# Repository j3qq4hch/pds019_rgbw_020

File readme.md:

# PDS019_lit20

В этом репозитории содержатся исходники устройства PDS019_rgbw_020.

Конструктивно устройство представляет из себя две печатные платы, размещенные в корпусе для монтажа на DIN-рейку [GAINTA D4MG](https://www.gainta.com/en/d4mg.html)

# Внешний вид платы А (верхней платы)

# Внешний вид платы B (нижней платы)

> [!IMPORTANT]
> Исходная документация (включая производственную документацию) хранится [здесь](https://github.com/j3qq4hch/pds019_rgbw_020/issues/1).

3d модель для онлайн просмотра доступна [по ссылке](https://a360.co/4bYYxEc)

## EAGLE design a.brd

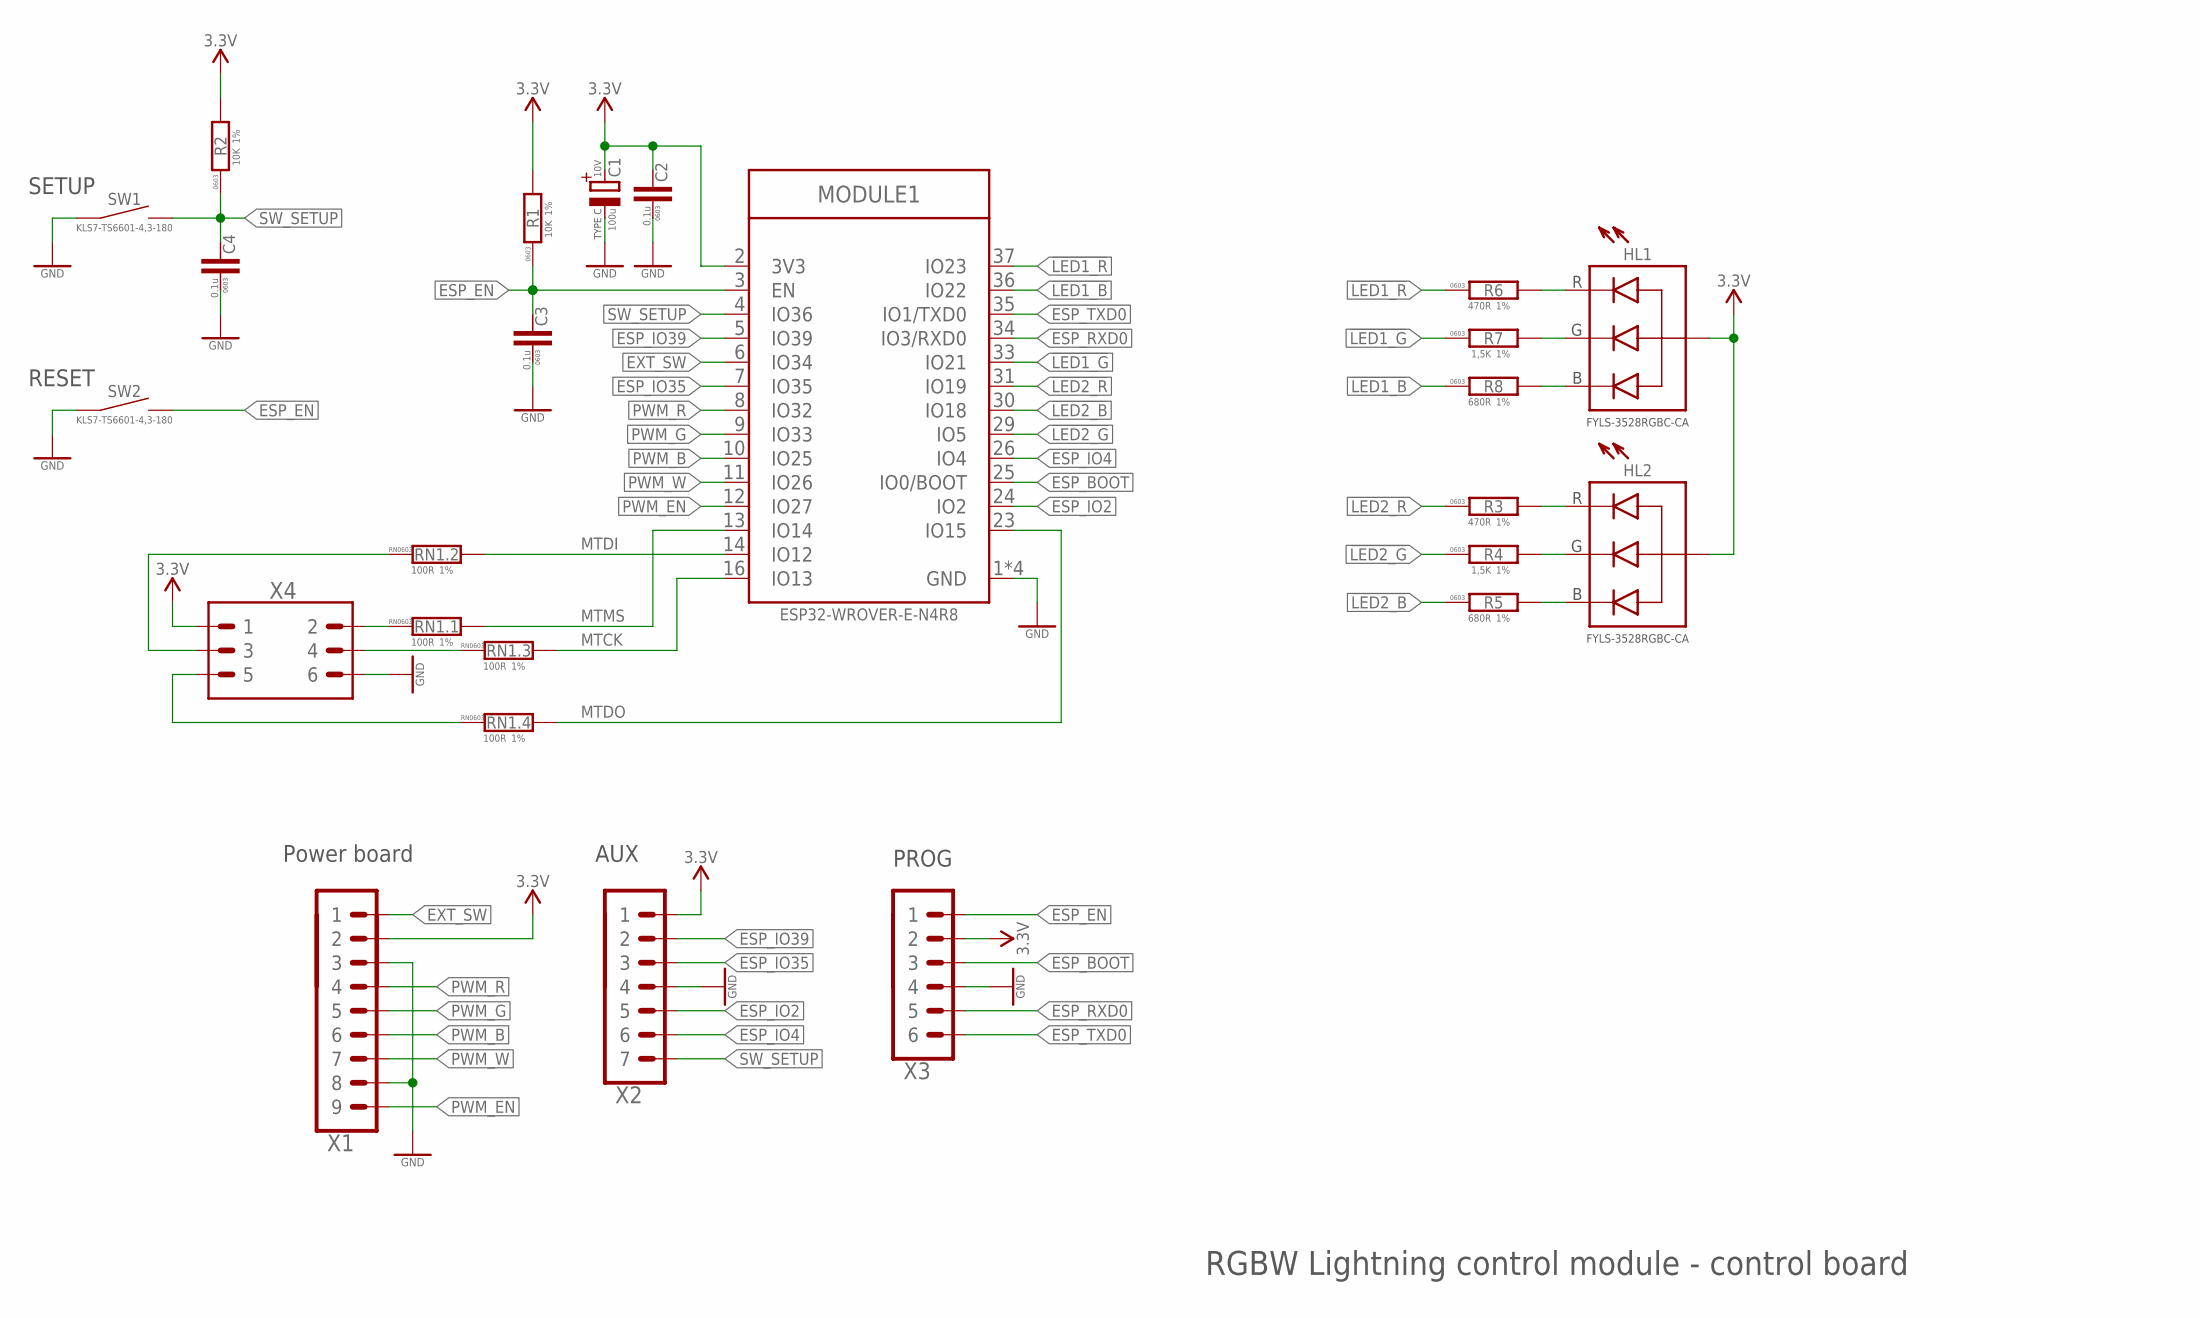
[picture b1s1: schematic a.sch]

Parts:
C1: 100u; CTANT_TYPE_C; VOLTAGE 10V
C2, C3, C4: 0.1u; C0603
HL1, HL2: LED_RGB-3528; LED3528
MODULE1: ESP32-WROVER-(I)E; ESP32-WROVER-E
R1, R2: 10K; R0603
R3, R6: 470R; R0603
R4, R7: 1,5K; R0603
R5, R8: 680R; R0603
RN1: 100R; R_4X0603
SW1, SW2: TS6601-9,5; SW4-6.0X6.0X5.0MM
X1: PINHEAD_1X09-2.54-TH-MALE; 1X09-PTH-2.54
X2: PINHEAD_1X07-2.54; 1X07-PTH-2.54
X3: PINHEAD_1X06-2-MALE; 1X06-PTH-2
X4: PINHEAD_2X03-PTH-2.54; 2X03-PTH-2.54

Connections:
!LED1_B: MODULE1.36 (IO22), R8.1
!LED1_G: MODULE1.33 (IO21), R7.1
!LED1_R: MODULE1.37 (IO23), R6.1
!LED2_B: MODULE1.30 (IO18), R5.1
!LED2_G: MODULE1.29 (IO5), R4.1
!LED2_R: MODULE1.31 (IO19), R3.1
ESP_BOOT: MODULE1.25 (IO0/BOOT), X3.3
ESP_EN: C3.2, MODULE1.3 (EN), R1.1, SW2.2, SW2.3 (2), X3.1
ESP_IO2: MODULE1.24 (IO2), X2.5
ESP_IO4: MODULE1.26 (IO4), X2.6
ESP_IO35: MODULE1.7 (IO35), X2.3
ESP_IO39: MODULE1.5 (IO39), X2.2
ESP_RXD0: MODULE1.34 (IO3/RXD0), X3.5
ESP_TXD0: MODULE1.35 (IO1/TXD0), X3.6
EXT_SW: MODULE1.6 (IO34), X1.1
GND: C1.-, C2.1, C3.1, C4.1, MODULE1.1 (GND), MODULE1.15 (GND), MODULE1.38 (GND), MODULE1.39 (GND), SW1.1, SW1.4 (1), SW2.1, SW2.4 (1), X1.3, X1.8, X2.4, X3.4, X4.6
MTCK: MODULE1.16 (IO13), RN1.6 (2)
MTDI: MODULE1.14 (IO12), RN1.7 (2)
MTDI_J: RN1.2 (1), X4.3
MTDO: MODULE1.23 (IO15), RN1.5 (2)
MTMS: MODULE1.13 (IO14), RN1.8 (2)
unnamed: HL2.1 (R), R3.2
unnamed: HL1.4 (G), R7.2
unnamed: HL1.1 (R), R6.2
unnamed: HL1.3 (B), R8.2
unnamed: HL2.4 (G), R4.2
unnamed: RN1.1, X4.2
unnamed: RN1.3 (1), X4.4
unnamed: RN1.4 (1), X4.5
unnamed: HL2.3 (B), R5.2
PWM_B: MODULE1.10 (IO25), X1.6
PWM_EN: MODULE1.12 (IO27), X1.9
PWM_G: MODULE1.9 (IO33), X1.5
PWM_R: MODULE1.8 (IO32), X1.4
PWM_W: MODULE1.11 (IO26), X1.7
SW_SETUP: C4.2, MODULE1.4 (IO36), R2.1, SW1.2, SW1.3 (2), X2.7
VDD_3V3: C1.+, C2.2, HL1.2 (A), HL2.2 (A), MODULE1.2 (3V3), R1.2, R2.2, X1.2, X2.1, X3.2, X4.1

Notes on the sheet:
RESET
SETUP
PROG
Power board
RGBW Lightning control module - control board
AUX

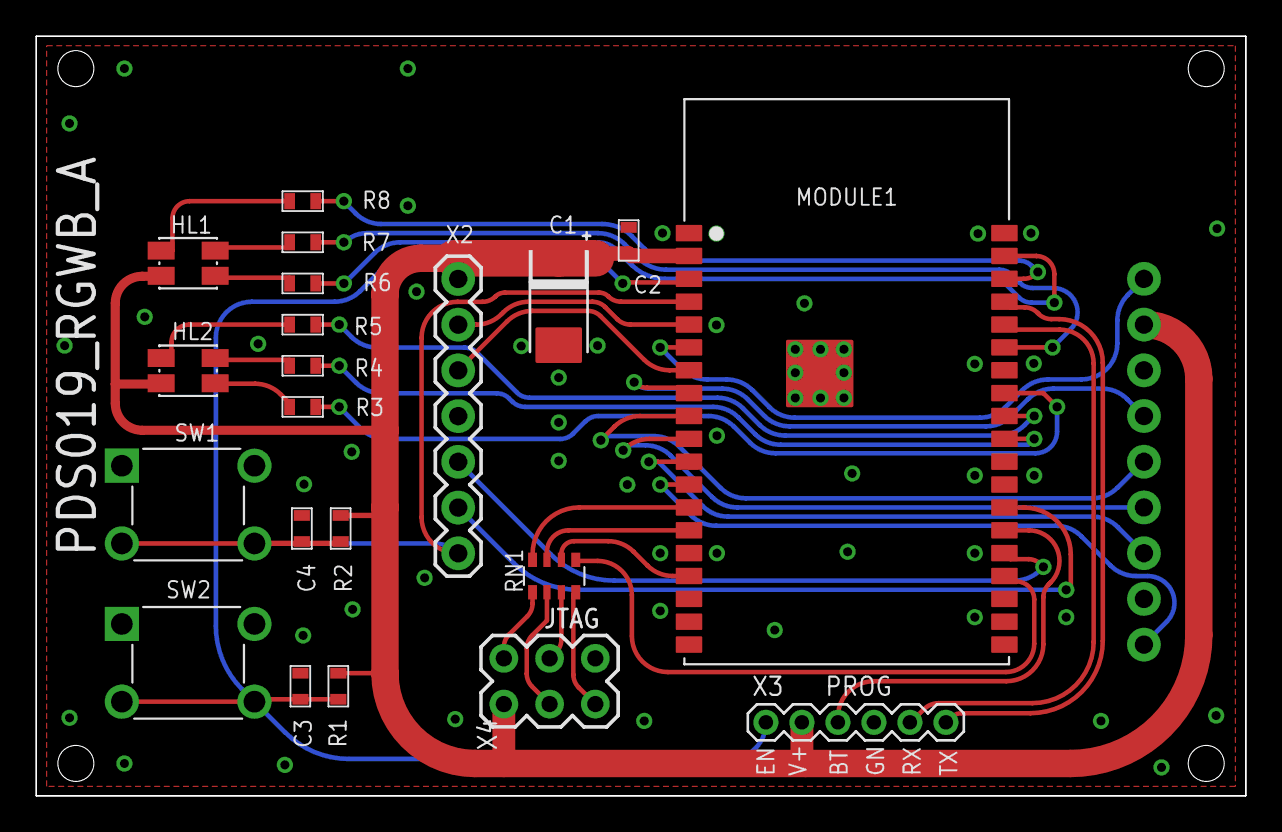
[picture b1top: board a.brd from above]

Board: 2 copper layers, 67.2 x 42.2 mm, 23 parts (1 on the bottom side), 37 nets.

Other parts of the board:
PCB1: D4MG_PCB_UP

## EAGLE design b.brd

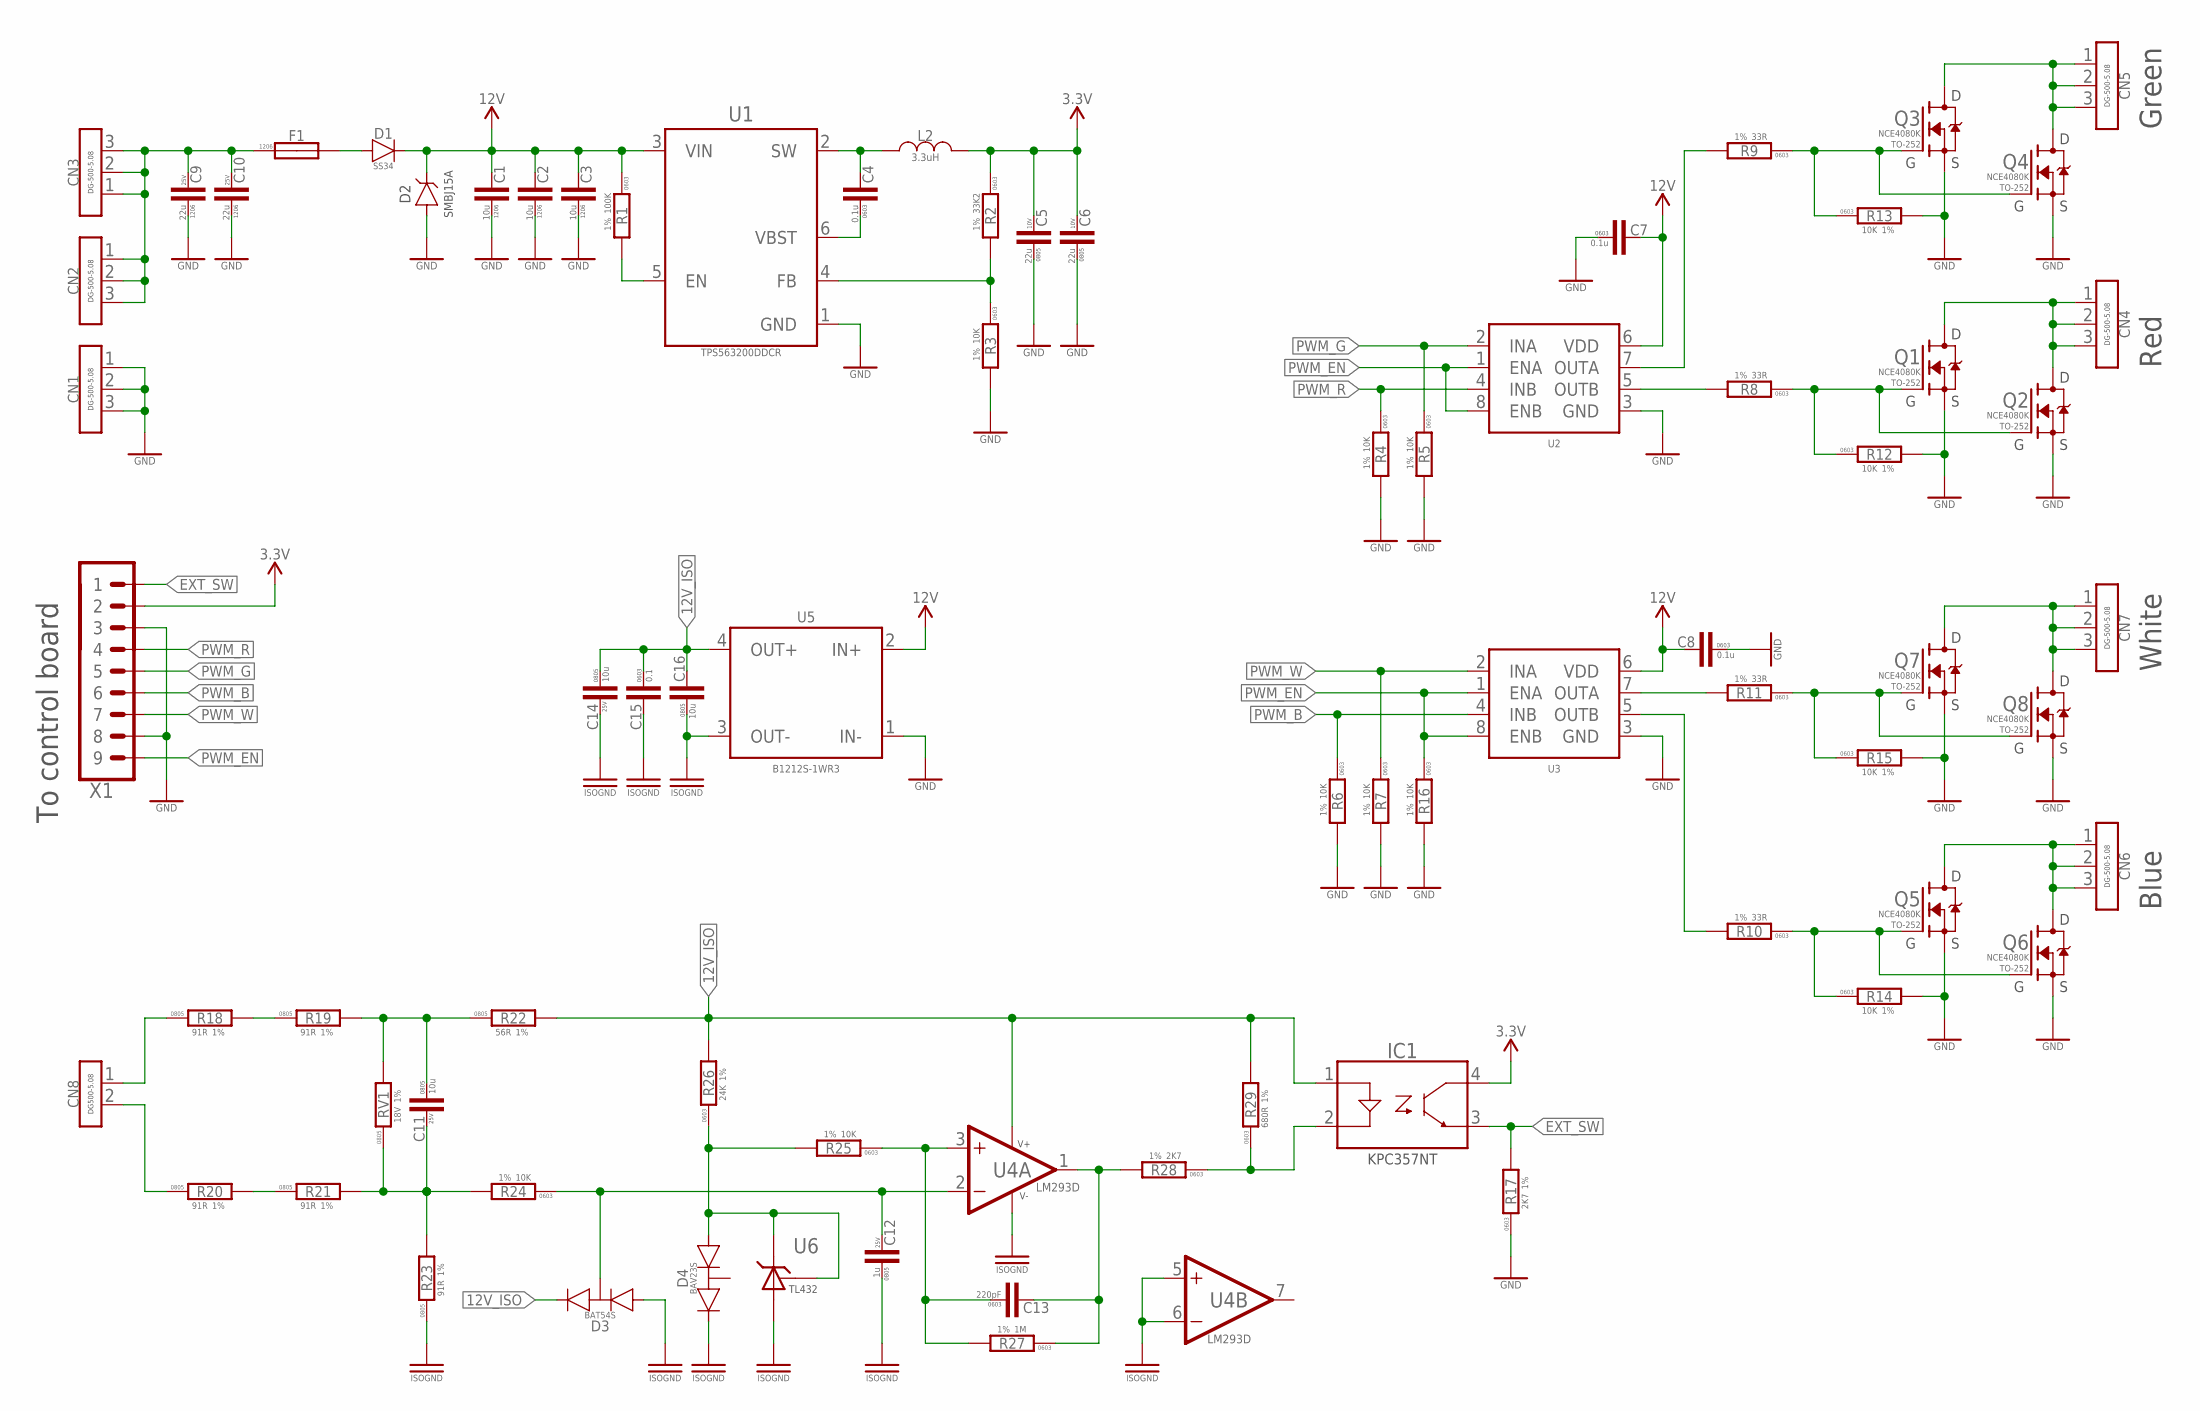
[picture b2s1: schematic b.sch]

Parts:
C1, C2, C3: 10u; C1206
C4, C7, C8: 0.1u; C0603
C5, C6: 22u; C0805; VOLTAGE 10V
C9, C10: 22u; C1206; VOLTAGE 25V
C11, C14: 10u; C0805; VOLTAGE 25V
C12: 1u; C0805; VOLTAGE 25V
C13: 220pF; C0603
C15: 0.1; C0603
C16: 10u; C0805
CN1, CN2, CN3, CN4, CN5, CN6, CN7: CON-3P-DG500-5.08; DG500-5.08-03P
CN8: DG508V-2P; DG500-5.08-02P
D1: SS24; DO-214AC(SMA)
D2: SMBJ15A-SMB; DO-214AA(SMB)
D3: BAT54S; SOT23
D4: BAV23S-SOT23; SOT23
F1: eFUSE-1206-500mA; F1206
IC1: KPC357NT-SOP-4; -SOP-4
L2: 3.3uH; SWPA6020
Q1, Q2, Q3, Q4, Q5, Q6, Q7, Q8: 100N04; D-PAK
R1: 100K; R0603
R2: 33K2; R0603
R3, R4, R5, R6, R7, R12, R13, R14, R15, R16, R24, R25: 10K; R0603
R8, R9, R10, R11: 33R; R0603
R17, R28: 2K7; R0603
R18, R19, R20, R21, R23: 91R; R0805
R22: 56R; R0805
R26: 24K; R0603
R27: 1M; R0603
R29: 680R; R0603
RV1: 18V; R0805
U1: TPS563200; SOT23-6
U2, U3: PN7762S; SOIC8
U4: LM293D; SOIC8
U5: B1212S-1WR3; SIP-4
U6: TL432; SOT23B-3
X1: PINHEAD_1X09-2.54-TH-MALE; 1X09-PTH-2.54

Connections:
12V_ISO: C14.1, C15.1, C16.2, D3.2 (C), IC1.1 (A), R22.2, R26.2, R29.2, U4.8 (V+), U5.4 (OUT+)
B_OUT: CN6.1, CN6.2, CN6.3, Q5.D, Q6.D
EXT_SW: IC1.3 (EMITTER), R17.2, X1.1
GND: C1.P$1 (1), C2.P$1 (1), C3.P$1 (1), C5.1, C6.1, C7.1, C8.1, C9.P$1 (1), C10.P$1 (1), CN1.1, CN1.2, CN1.3, D2.A, Q1.S, Q2.S, Q3.S, Q4.S, Q5.S, Q6.S, Q7.S, Q8.S, R3.2, R4.2, R5.2, R6.2, R7.2, R12.2, R13.2, R14.2, R15.2, R16.2, R17.1, U1.1 (GND), U2.3 (GND), U3.3 (GND), U5.1 (IN-), X1.3, X1.8
G_OUT: CN5.1, CN5.2, CN5.3, Q3.D, Q4.D
ISOGND: C12.1, C14.2, C15.2, C16.1, D3.1 (A), D4.2 (C), R23.1, U4.4 (V-), U4.5 (IN+), U4.6 (IN-), U5.3 (OUT-), U6.3 (A)
unnamed: Q1.G, Q2.G, R8.1, R12.1
unnamed: R1.2, U1.5 (EN)
unnamed: Q3.G, Q4.G, R9.1, R13.1
unnamed: D1.A, F1.P$2 (2)
unnamed: R11.2, U3.7 (OUTA)
unnamed: R10.2, U3.5 (OUTB)
unnamed: R8.2, U2.5 (OUTB)
unnamed: Q5.G, Q6.G, R10.1, R14.1
unnamed: Q7.G, Q8.G, R11.1, R15.1
unnamed: C4.1, U1.6 (VBST)
unnamed: R9.2, U2.7 (OUTA)
unnamed: C4.2, L2.1, U1.2 (SW)
unnamed: IC1.2 (C), R28.1, R29.1
unnamed: R2.2, R3.1, U1.4 (FB)
unnamed: C13.2, R27.1, R28.2, U4.1 (OUT)
unnamed: C12.2, D3.3 (COMMON), R24.1, U4.2 (IN-)
unnamed: C11.1, R19.2, R22.1, RV1.2
unnamed: R18.2, R19.1
unnamed: R20.2, R21.1
unnamed: C13.1, R25.1, R27.2, U4.3 (IN+)
unnamed: D4.1 (A), R25.2, R26.1, U6.1 (R), U6.2 (C)
unnamed: C11.2, R21.2, R23.2, R24.2, RV1.1
PWM_B: R6.1, U3.4 (INB), X1.6
PWM_EN: R16.1, U2.1 (ENA), U2.8 (ENB), U3.1 (ENA), U3.8 (ENB), X1.9
PWM_G: R5.1, U2.2 (INA), X1.5
PWM_R: R4.1, U2.4 (INB), X1.4
PWM_W: R7.1, U3.2 (INA), X1.7
R_OUT: CN4.1, CN4.2, CN4.3, Q1.D, Q2.D
SW_IN+: CN8.1, R18.1
SW_IN-: CN8.2, R20.1
V+: C9.P$2 (2), C10.P$2 (2), CN2.1, CN2.2, CN2.3, CN3.1, CN3.2, CN3.3, F1.P$1 (1)
VDD_3V3: C5.2, C6.2, IC1.4 (COLLECTOR), L2.2, R2.1, X1.2
VDD_12V: C1.P$2 (2), C2.P$2 (2), C3.P$2 (2), C7.2, C8.2, D1.C, D2.C, R1.1, U1.3 (VIN), U2.6 (VDD), U3.6 (VDD), U5.2 (IN+)
Y_OUT: CN7.1, CN7.2, CN7.3, Q7.D, Q8.D

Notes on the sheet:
To control board
Red
Green
Blue
White

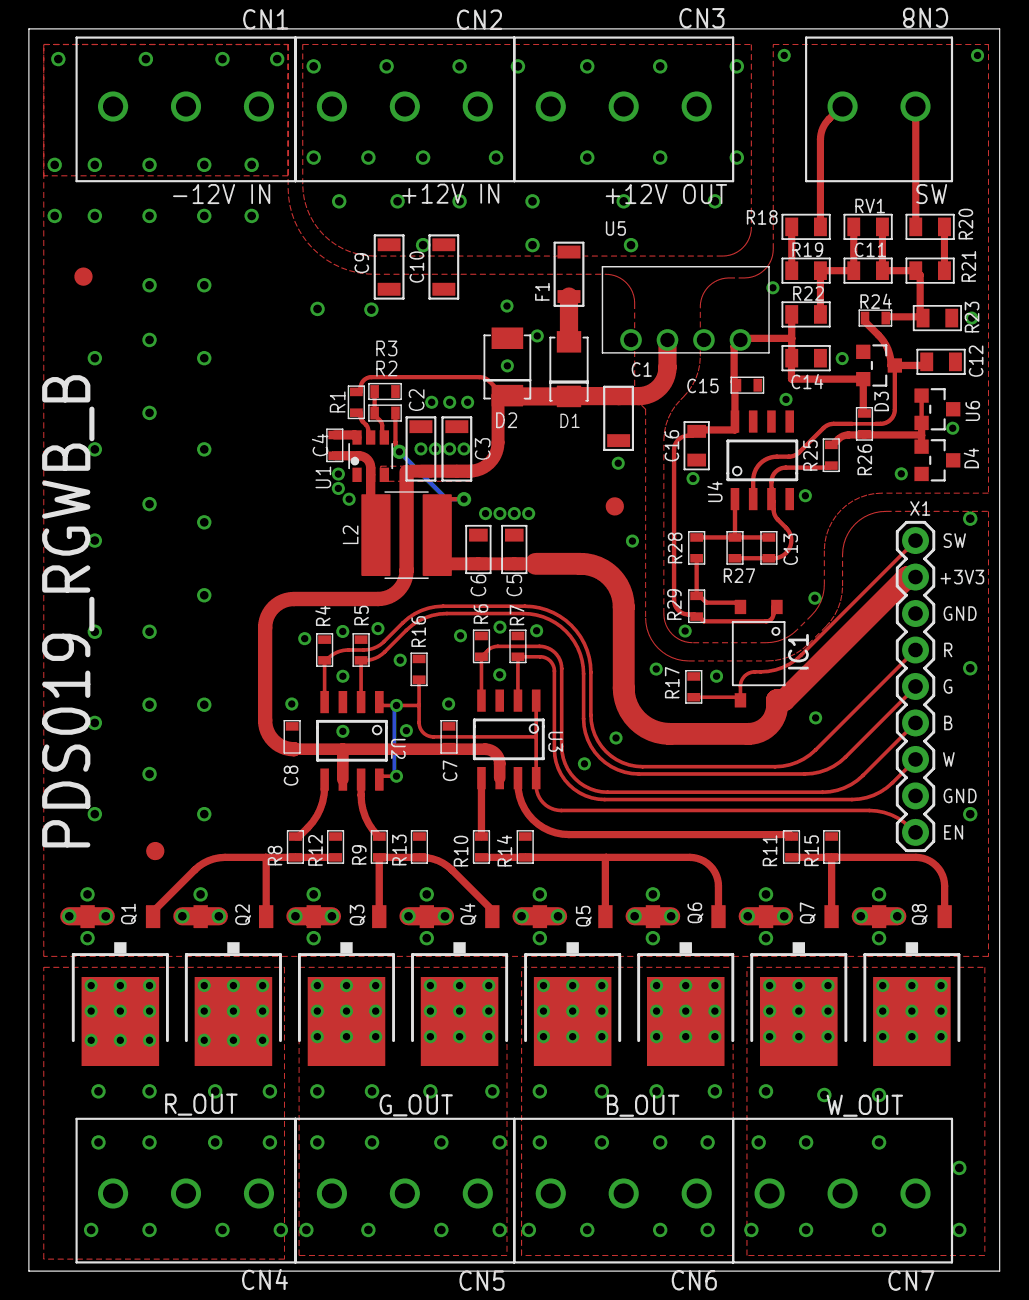
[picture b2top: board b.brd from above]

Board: 2 copper layers, 67.6 x 86.5 mm, 80 parts (0 on the bottom side), 40 nets.

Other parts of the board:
PCB1: D4MG_PCB
REP1, REP2, REP3: REF_POINT_D1.27_D3.81

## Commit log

2026-04-03 initial import
2026-04-03 a pcb
2026-04-03 more import
